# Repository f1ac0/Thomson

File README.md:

# Thomson
Kids in the 80's in France discovered computers at school with the TO and MO series from Thomson.

Interesting expansions exist to enjoy these systems, see below.

In this repository I share the boards I modified for my own needs, for example to use the parts I have in stock, or because I like my own routing.

# Disclaimer and Acknowledgements
This is a hobbyist project, it comes with no warranty and no support. Also remember that the Commodore machines are about 40 years old and may fail because of such hardware expansions.

I publish my work under the CC-BY-NC-SA license, unless stated otherwise. Thanks to everyone who share their knowledge and creations.

# Sources and interesting projects
## Cartridges
- https://dcmoto.pages-perso.free.fr/bricolage/memo7/index.html

## RAM
- https://www.forum.system-cfg.com/viewtopic.php?f=18&t=10807

## Expansions
- https://dcmoto.pages-perso.free.fr/bricolage/sddrive/index.html
- https://dcmoto.pages-perso.free.fr/bricolage/sx90-2018/index.html

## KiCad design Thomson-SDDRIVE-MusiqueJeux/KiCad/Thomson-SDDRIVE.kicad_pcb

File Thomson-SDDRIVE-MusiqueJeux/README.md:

# Thomson-SDDRIVE-MusiqueJeu
This is an expansion combining the SX90-018 "Contrôleur d'extensions modèle 2" that provides a 6 bit DAC for sound and two DB9 joystick ports and the SDDRIVE that emulates a floppy disk controller. The logic is integrated inside a XC9572XL CPLD and using SMD components to reduce size.

Warning : the two joystick ports use an "Atari" pinout and not the specific thomson-only pinout of the original expansion. Make sure to use standard controllers and not Thomson ones if you own any (I dont). 5V is present so you may use powered controllers, but make sure to use limited power to preserve your host PSU and motherboard.

# Disclaimer and Acknowledgements
This is a hobbyist project, it comes with no warranty and no support. Also remember that the Thomson machines are about 40 years old and may fail because of such hardware expansions.

The author of SDDRIVE keeps the intellectual property of his work and gracefully shares his degigns and agrees that users change, improve and share them, and forbids commercial use and selling the products. the content inside this folder is published under the same licensing terms.

It is not supported by the author of SDDRIVE, please don't bother him with issues you might have with it.

# From original designs by
- SDDRIVE by Daniel Coulom : https://dcmoto.pages-perso.free.fr/bricolage/sddrive/index.html
- SX90-018 by Thomson, schematics reverse engineered by Daniel Coulom for his SX90-2018 : https://dcmoto.pages-perso.free.fr/bricolage/sx90-2018/index.html
Thanks !

# Making it
Components are SMD, and have thin pin pitch. You need to know what you are doing.

Check for shorts at least between 5V, 3.3V, and GND traces before applying power ! I suggest to first install the CPLD and check its connections, then the PLCC socket and also check its connections, before the SD socket and through holes connectors that will maker rework more difficult.

Make sure to apply insulating tape under the SD socket where the contacts from the socket may touch the PCB. In order to keep the two layer PCB, this was not possible to use no copper zone there.

For the edge connector, I used a 2x21=42 pins connecto because I could not find an 2x19 one. If you do so then make sure to remove the four pins on the edges and insert a small piece of PCB to force the connector to be aligned with the PCB edge when inserted.

The ROM is oversized however easily available. You have to program it with the original sddrive_control.bin using an EEPROM programmer. Pad the end of the file up to a size of 524288 or tell your programmer to only burn the lower bytes since the higher addresses are grounded anyway.

Prepare the SDCARD as explained on the SDDRIVE page.

# Using it
Connect it to your Thomson. When the system is starting, it should show the disk drive menu that will start the selector. See the instructions for SDDRIVE, it should behave the same.

# FD2SD
You can use SD files that are compatible with your system. You will find some on the dcmoto website. You can also convert some .FD disk images.

The DCMOTO emulator provides a FD2SD windows tool, if you use a different system you may use the FD2SD in this repo.

Compile it with "gcc -o fd2sd fd2sd.c" then convert a file with "fd2sd file.fd". Check other usage with "fd2sd -h".

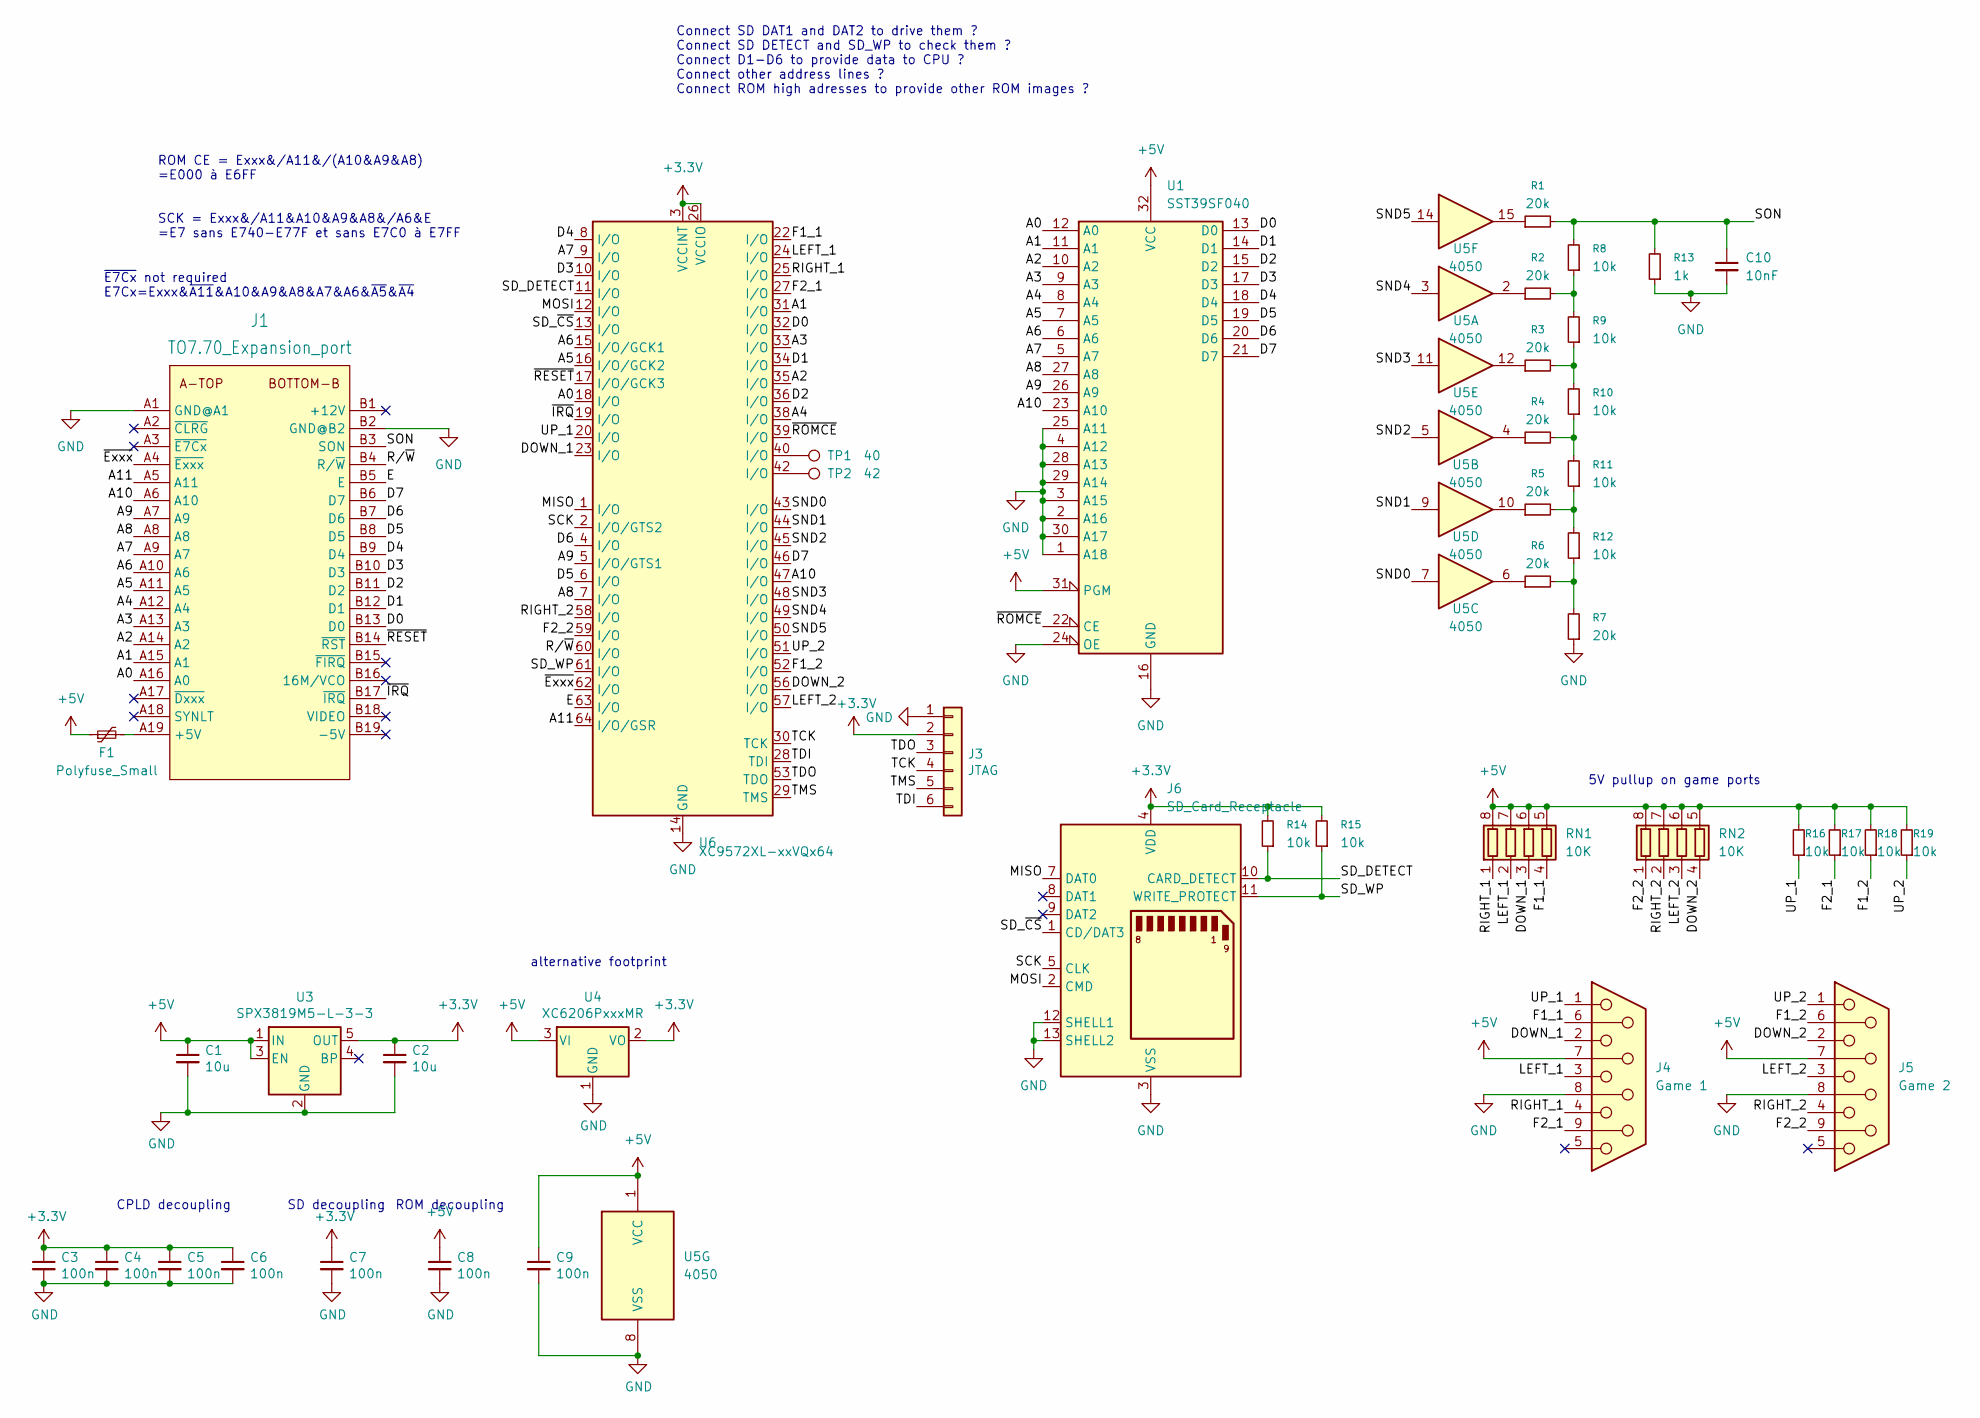
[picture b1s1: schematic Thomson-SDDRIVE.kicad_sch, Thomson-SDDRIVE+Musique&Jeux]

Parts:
C1, C2: 10u; C_0805_2012Metric
C3, C4, C5, C6, C7, C8, C9: 100n; C_0805_2012Metric
C10: 10nF; C_0805_2012Metric
F1: Polyfuse_Small; R_1210_3225Metric
J1: TO7.70_Expansion_port; TO7.70_Expansion_port_Minibus_3x19_P2.54mm_W5.08mm_Vertical
J3: JTAG; PinHeader_1x06_P2.54mm_Vertical
J4: Game 1; DSUB-9_Pins_Vertical_P2.77x2.84mm
J5: Game 2; DSUB-9_Pins_Vertical_P2.77x2.84mm
J6: SD_Card_Receptacle; Conn_SDcard_largerpads
R1, R2, R3, R4, R5, R6, R7: 20k; R_0805_2012Metric
R8, R9, R10, R11, R12, R14, R15, R16, R17, R18, R19: 10k; R_0805_2012Metric
R13: 1k; R_0805_2012Metric
RN1, RN2: 10K; R_Array_Convex_4x0603
TP1: 40; Measurement_Point_Round-SMD-Pad_VerySmall
TP2: 42; Measurement_Point_Round-SMD-Pad_VerySmall
U1: SST39SF040; PLCC-32_SMD-Socket
U3: SPX3819M5-L-3-3; SOT-23-5
U4: XC6206PxxxMR; SOT-23
U5: 4050; SOIC-16_3.9x9.9mm_P1.27mm
U6: XC9572XL-xxVQx64; TQFP-64_10x10mm_P0.5mm

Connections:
+3.3V: C2.1, C3.1, C4.1, C5.1, C6.1, C7.1, J3.2, J6.4 (VDD), R14.2, R15.2, U3.5 (OUT), U4.2 (VO), U6.3 (VCCINT), U6.26 (VCCIO), U6.37 (VCCINT), U6.55 (VCCIO)
+5V: C1.1, C8.1, C9.1, F1.1, J4.7, J5.7, R16.2, R17.2, R18.2, R19.2, RN1.5 (R4.2), RN1.6 (R3.2), RN1.7 (R2.2), RN1.8 (R1.2), RN2.5 (R4.2), RN2.6 (R3.2), RN2.7 (R2.2), RN2.8 (R1.2), U1.31 (PGM), U1.32 (VCC), U3.1 (IN), U3.3 (EN), U4.3 (VI), U5.1 (VCC)
/A0: J1.A16 (A0), U1.12 (A0), U6.18 (I/O)
/A1: J1.A15 (A1), U1.11 (A1), U6.31 (I/O)
/A2: J1.A14 (A2), U1.10 (A2), U6.35 (I/O)
/A3: J1.A13 (A3), U1.9 (A3), U6.33 (I/O)
/A4: J1.A12 (A4), U1.8 (A4), U6.38 (I/O)
/A5: J1.A11 (A5), U1.7 (A5), U6.16 (I/O/GCK2)
/A6: J1.A10 (A6), U1.6 (A6), U6.15 (I/O/GCK1)
/A7: J1.A9 (A7), U1.5 (A7), U6.9 (I/O)
/A8: J1.A8, U1.27 (A8), U6.7 (I/O)
/A9: J1.A7 (A9), U1.26 (A9), U6.5 (I/O/GTS1)
/A10: J1.A6 (A10), U1.23 (A10), U6.47 (I/O)
/A11: J1.A5 (A11), U6.64 (I/O/GSR)
/D0: J1.B13 (D0), U1.13 (D0), U6.32 (I/O)
/D1: J1.B12 (D1), U1.14 (D1), U6.34 (I/O)
/D2: J1.B11 (D2), U1.15 (D2), U6.36 (I/O)
/D3: J1.B10 (D3), U1.17 (D3), U6.10 (I/O)
/D4: J1.B9 (D4), U1.18 (D4), U6.8 (I/O)
/D5: J1.B8 (D5), U1.19 (D5), U6.6 (I/O)
/D6: J1.B7 (D6), U1.20 (D6), U6.4 (I/O)
/D7: J1.B6 (D7), U1.21 (D7), U6.46 (I/O)
/DOWN_1: J4.2, RN1.3 (R3.1), U6.23 (I/O)
/DOWN_2: J5.2, RN2.4 (R4.1), U6.56 (I/O)
/E: J1.B5 (E), U6.63 (I/O)
/F1_1: J4.6, RN1.4 (R4.1), U6.22 (I/O)
/F1_2: J5.6, R18.1, U6.52 (I/O)
/F2_1: J4.9, R17.1, U6.27 (I/O)
/F2_2: J5.9, RN2.1 (R1.1), U6.59 (I/O)
/LEFT_1: J4.3, RN1.2 (R2.1), U6.24 (I/O)
/LEFT_2: J5.3, RN2.3 (R3.1), U6.57 (I/O)
/MISO: J6.7 (DAT0), U6.1 (I/O)
/MOSI: J6.2 (CMD), U6.12 (I/O)
/RIGHT_1: J4.4, RN1.1 (R1.1), U6.25 (I/O)
/RIGHT_2: J5.4, RN2.2 (R2.1), U6.58 (I/O)
/R/~W: J1.B4 (R/~W), U6.60 (I/O)
/SCK: J6.5 (CLK), U6.2 (I/O/GTS2)
/SD_DETECT: J6.10 (CARD_DETECT), R14.1, U6.11 (I/O)
/SD_WP: J6.11 (WRITE_PROTECT), R15.1, U6.61 (I/O)
/SD_~CS: J6.1 (CD/DAT3), U6.13 (I/O)
/SND0: U5.7, U6.43 (I/O)
/SND1: U5.9, U6.44 (I/O)
/SND2: U5.5, U6.45 (I/O)
/SND3: U5.11, U6.48 (I/O)
/SND4: U5.3, U6.49 (I/O)
/SND5: U5.14, U6.50 (I/O)
/SON: C10.1, J1.B3 (SON), R1.2, R8.2, R13.2
/TCK: J3.4, U6.30 (TCK)
/TDI: J3.6, U6.28 (TDI)
/TDO: J3.3, U6.53 (TDO)
/TMS: J3.5, U6.29 (TMS)
/UP_1: J4.1, R16.1, U6.20 (I/O)
/UP_2: J5.1, R19.1, U6.51 (I/O)
/~Exxx: J1.A4 (~Exxx), U6.62 (I/O)
/~IRQ: J1.B17 (~IRQ), U6.19 (I/O)
/~RESET: J1.B14 (~RST), U6.17 (I/O/GCK3)
/~ROMCE: U1.22 (CE), U6.39 (I/O)
GND: C1.2, C2.2, C3.2, C4.2, C5.2, C6.2, C7.2, C8.2, C9.2, C10.2, J1.A1 (GND@A1), J1.B2 (GND@B2), J3.1, J4.8, J5.8, J6.3 (VSS), J6.6 (VSS), J6.12 (SHELL1), J6.13 (SHELL2), R7.1, R13.1, U1.1 (A18), U1.2 (A16), U1.3 (A15), U1.4 (A12), U1.16 (GND), U1.24 (OE), U1.25 (A11), U1.28 (A13), U1.29 (A14), U1.30 (A17), U3.2 (GND), U4.1 (GND), U5.8 (VSS), U6.14 (GND), U6.21 (GND), U6.41 (GND), U6.54 (GND)
unnamed: F1.2, J1.A19 (+5V)
unnamed: R1.1, U5.15
unnamed: R2.1, U5.2
unnamed: R2.2, R8.1, R9.2
unnamed: R3.1, U5.12
unnamed: R4.1, U5.4
unnamed: R5.1, U5.10
unnamed: R6.1, U5.6
unnamed: R4.2, R10.1, R11.2
unnamed: R3.2, R9.1, R10.2
unnamed: R5.2, R11.1, R12.2
unnamed: R6.2, R7.2, R12.1
unnamed: TP1.1, U6.40 (I/O)
unnamed: TP2.1, U6.42 (I/O)

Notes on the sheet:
~{E7Cx} not required E7Cx=Exxx&~{A11}&A10&A9&A8&A7&A6&~{A5}&~{A4}
5V pullup on game ports
SD decoupling
ROM CE = Exxx&/A11&/(A10&A9&A8) =E000 à E6FF SCK = Exxx&/A11&A10&A9&A8&/A6&E =E7 sans E740-E77F et sans E7C0 à E7FF
alternative footprint
CPLD decoupling
Connect SD DAT1 and DAT2 to drive them ? Connect SD DETECT and SD_WP to check them ? Connect D1-D6 to provide data to CPU ? Connect other address lines ? Connect ROM high adresses to provide other ROM images ?
ROM decoupling

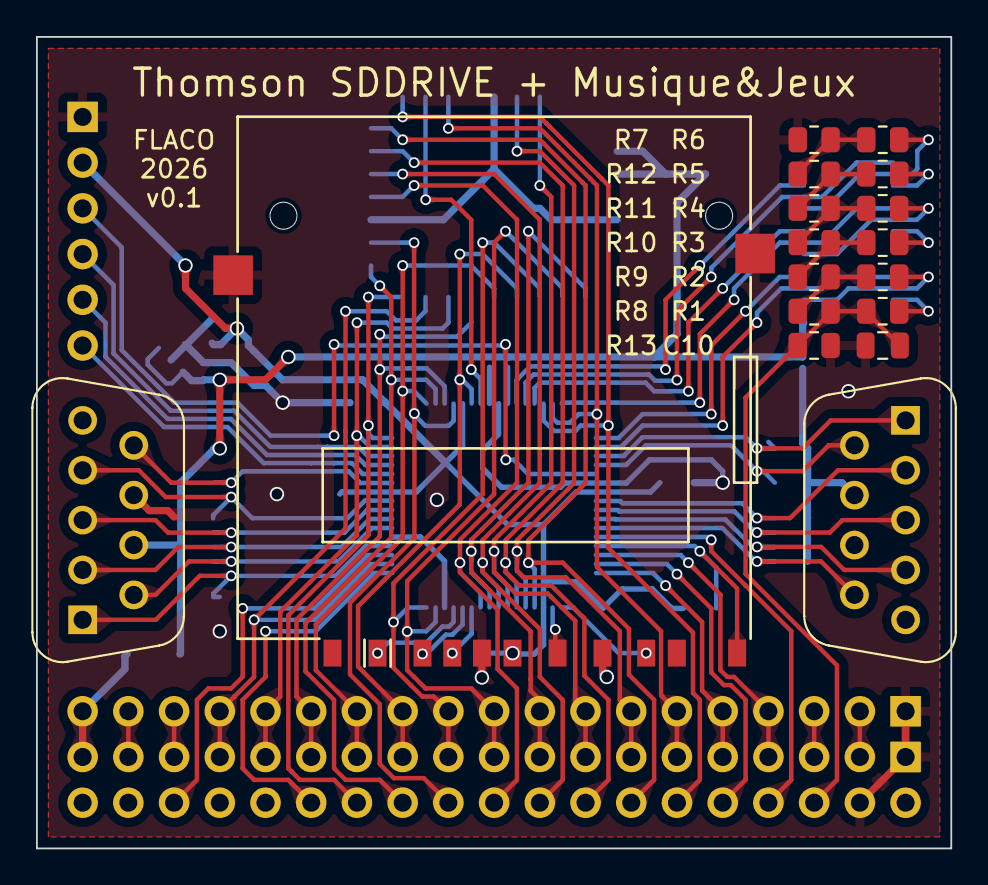
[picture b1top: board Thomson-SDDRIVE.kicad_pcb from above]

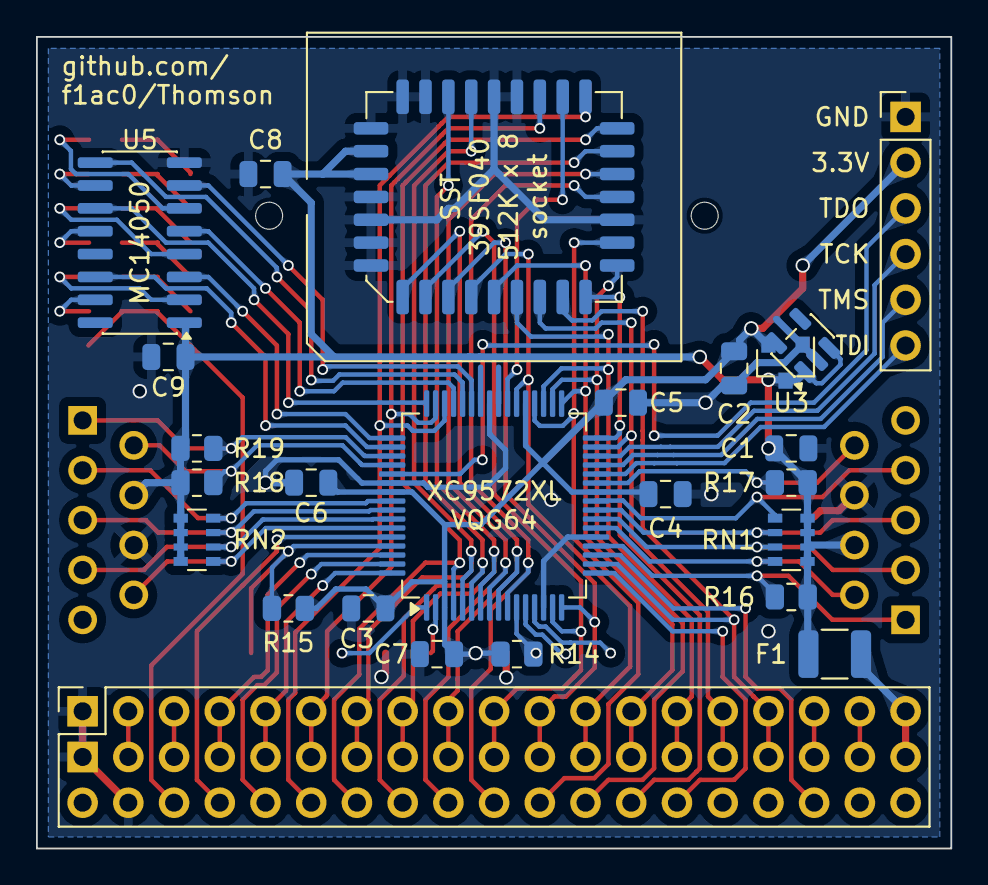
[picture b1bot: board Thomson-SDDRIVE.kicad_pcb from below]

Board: 2 copper layers, 50.8 x 45.1 mm, 42 parts (25 on the bottom side), 70 nets.

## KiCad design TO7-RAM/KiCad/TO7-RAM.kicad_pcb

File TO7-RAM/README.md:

# TO7-RAM
A 64K RAM for the TO7/70, adding 4 banks of 16kB. Basic 128 now reports 128K of RAM and TEST64K-TO770 Memo7 says banks 2-7 are OK. Not sure it is useful for anything else yet.

# Disclaimer and Acknowledgements
This is a hobbyist project, it comes with no warranty and no support. Also remember that the Commodore machines are about 40 years old and may fail because of such hardware expansions.

I publish my work under the CC-BY-NC-SA license, unless stated otherwise. Thanks to everyone who share their knowledge and creations.

# Original design
- https://www.forum.system-cfg.com/viewtopic.php?f=18&t=10807
Thanks 6502man, Daniel and Fred_72 !

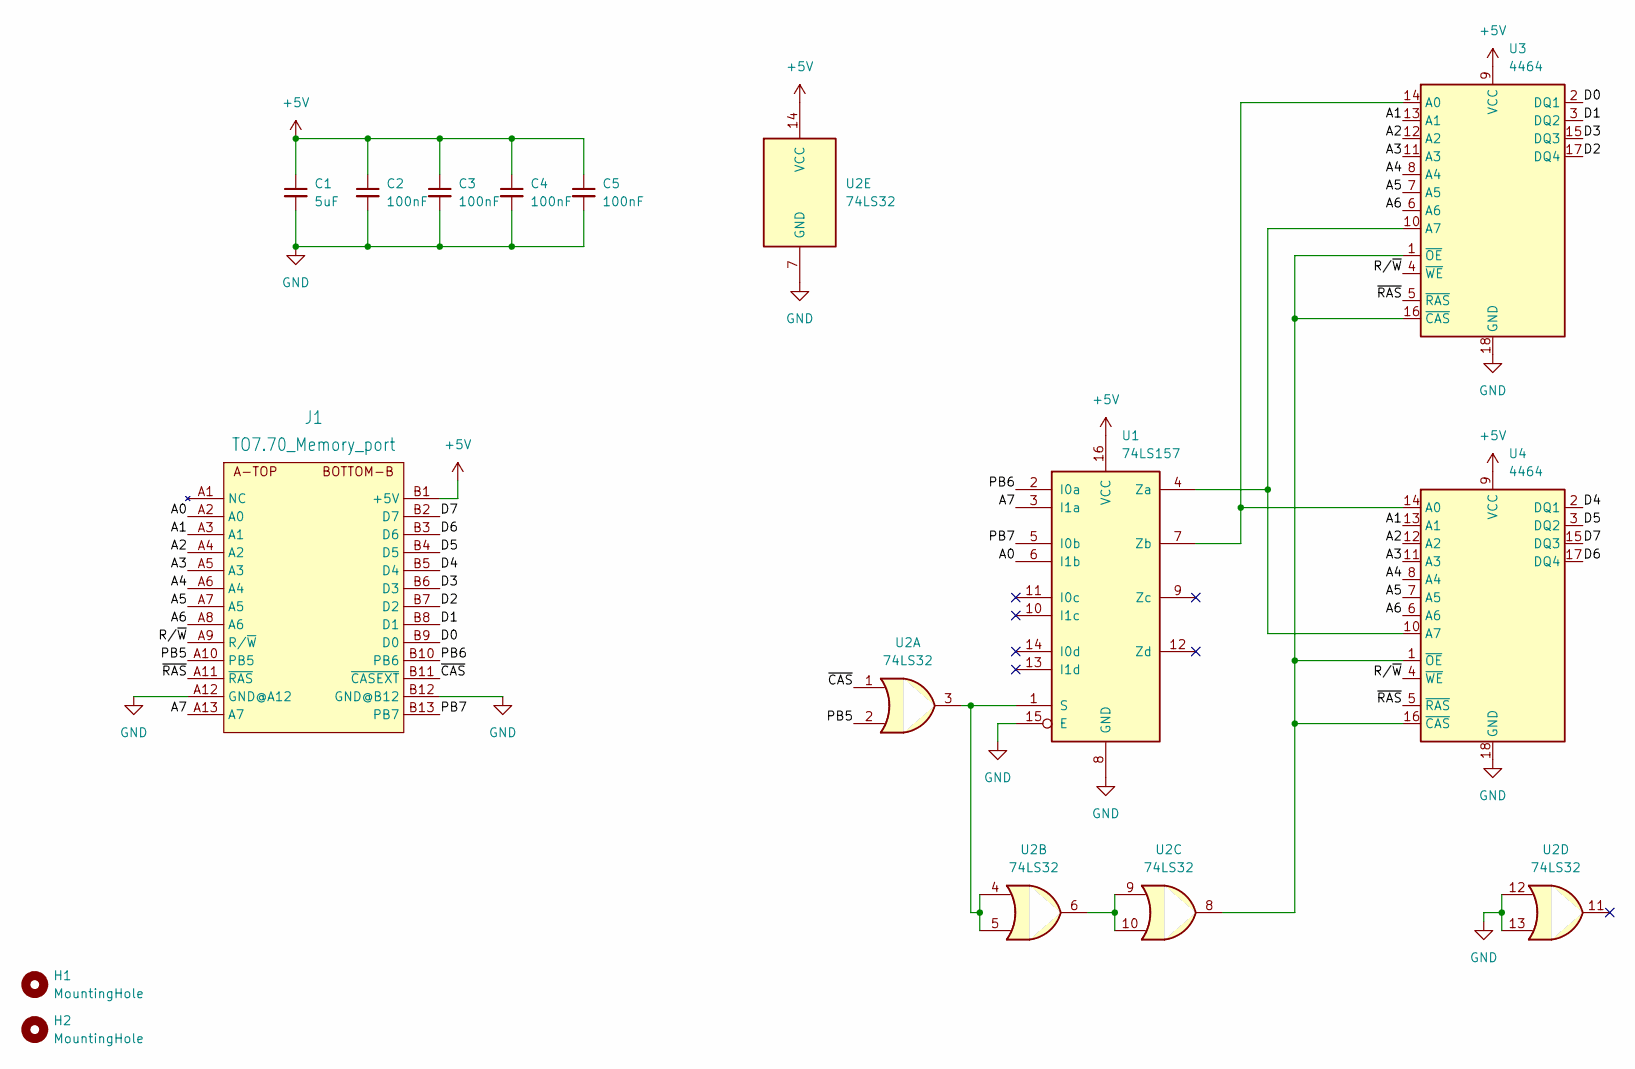
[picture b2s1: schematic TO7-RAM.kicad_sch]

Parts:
C1: 5uF; C_0805_2012Metric
C2, C3, C4, C5: 100nF; C_0805_2012Metric
H1, H2: MountingHole; MountingHole_4mm
J1: TO7.70_Memory_port; TO7.70_Memory_port_2x13_P2.54mm_W5.08mm_Vertical
U1: 74LS157; DIP-16_W7.62mm
U2: 74LS32; DIP-14_W7.62mm
U3, U4: 4464; DIP-18_W7.62mm_Socket

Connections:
+5V: C1.1, C2.1, C3.1, C4.1, C5.1, J1.B1 (+5V), U1.16 (VCC), U2.14 (VCC), U3.9 (VCC), U4.9 (VCC)
/A0: J1.A2 (A0), U1.6 (I1b)
/A1: J1.A3 (A1), U3.13 (A1), U4.13 (A1)
/A2: J1.A4 (A2), U3.12 (A2), U4.12 (A2)
/A3: J1.A5 (A3), U3.11 (A3), U4.11 (A3)
/A4: J1.A6 (A4), U3.8 (A4), U4.8 (A4)
/A5: J1.A7 (A5), U3.7 (A5), U4.7 (A5)
/A6: J1.A8 (A6), U3.6 (A6), U4.6 (A6)
/A7: J1.A13 (A7), U1.3 (I1a)
/D0: J1.B9 (D0), U3.2 (DQ1)
/D1: J1.B8 (D1), U3.3 (DQ2)
/D2: J1.B7 (D2), U3.17 (DQ4)
/D3: J1.B6 (D3), U3.15 (DQ3)
/D4: J1.B5 (D4), U4.2 (DQ1)
/D5: J1.B4 (D5), U4.3 (DQ2)
/D6: J1.B3 (D6), U4.17 (DQ4)
/D7: J1.B2 (D7), U4.15 (DQ3)
/PB5: J1.A10 (PB5), U2.2
/PB6: J1.B10 (PB6), U1.2 (I0a)
/PB7: J1.B13 (PB7), U1.5 (I0b)
/R/~W: J1.A9 (R/~W), U3.4 (~WE), U4.4 (~WE)
/~CAS: J1.B11 (~CASEXT), U2.1
/~RAS: J1.A11 (~RAS), U3.5 (~RAS), U4.5 (~RAS)
GND: C1.2, C2.2, C3.2, C4.2, C5.2, J1.A12 (GND@A12), J1.B12 (GND@B12), U1.8 (GND), U1.15 (E), U2.7 (GND), U2.12, U2.13, U3.18 (GND), U4.18 (GND)
unnamed: U1.1 (S), U2.3, U2.4, U2.5
unnamed: U1.4 (Za), U3.10 (A7), U4.10 (A7)
unnamed: U1.7 (Zb), U3.14 (A0), U4.14 (A0)
unnamed: U2.6, U2.9, U2.10
unnamed: U2.8, U3.1 (~OE), U3.16 (~CAS), U4.1 (~OE), U4.16 (~CAS)

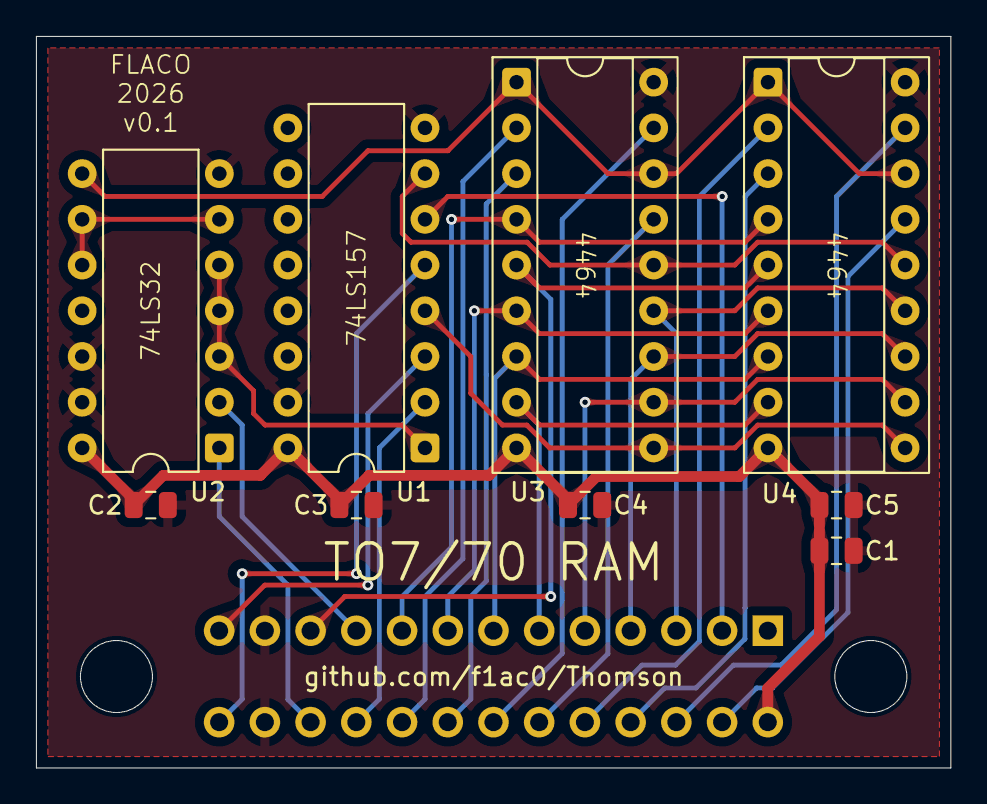
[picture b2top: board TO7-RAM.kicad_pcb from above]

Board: 2 copper layers, 50.8 x 40.6 mm, 12 parts (1 on the bottom side), 29 nets.

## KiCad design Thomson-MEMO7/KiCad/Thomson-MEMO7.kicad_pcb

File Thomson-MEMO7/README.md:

# Thomson-MEMO7
A multi-ROM Memo7 for the TO7 computer.
- 32x 16k banks
- 32k and 64k using bank switching
- 3D printed case

# Disclaimer and Acknowledgements
This is a hobbyist project, it comes with no warranty and no support. Also remember that the Commodore machines are about 40 years old and may fail because of such hardware expansions.

I publish my work under the CC-BY-NC-SA license, unless stated otherwise. Thanks to everyone who share their knowledge and creations.

# Inspired by
- https://dcmoto.pages-perso.free.fr/bricolage/memo7/index.html
- https://forum.system-cfg.com/viewtopic.php?f=10&t=7086
- https://www.thingiverse.com/thing:5231941
Thanks !

# Making it
- Install the DIP switch so that the switches are closed when the lever is LOW
- Check for shorts at least between 5V, and GND traces before applying power! Also check that R4 and R5 are not shorted : if they are then the pins of the ROM socket are shorted to the nearby 5V pin and setting A17/A18 switch to LOW will short 5V to ground!

To prepare the ROM image,
- select 16k, 32k and 64k files to fill the 512k ROM chip and decide their order in the ROM,
- for 32k and 64k files, make sure they will start respectively on 32k and 64k boundaries,
- for 4k and 8k file, duplicate them 4 times and 2 times respectively,
- for files that are shorter than 16k, pad them up to the full size,
- concatenate them into one single file,
- burn the file into the EEPROM.

For example on linux : cat 16krom.m7 4krom.m7 4krom.m7 4krom.m7 4krom.m7 32krom.m7 64krom.m7 (...) >romfile

I suggest to print the content of the ROM with the correct switch placement to remember it later:
- LLLLLHH 16krom
- LLLLHHH 4krom
- LLLHHLH 32krom
- LLHHHLL 64krom
- ...

# Using it
Choose the ROM while the system is powered down.
- To select a 16k ROM, dial its address on the A14 to A18 switches. Set the 32k and 64k switches UP.
- To select a 32K ROM, dial its address on the A15 to A18 switches. Set A14 UP and 32k LOW.
- To select a 64K ROM, dial its address on the A16 to A18 switches. Set A14 and A15 UP then 32k and 64k LOW.

Make sure to always set A14 UP when 32K is LOW, and A15 UP when 64k is LOW: failing to do so and setting them LOW at the same time will short to ground the outputs of the 74LS173 and may damage them.

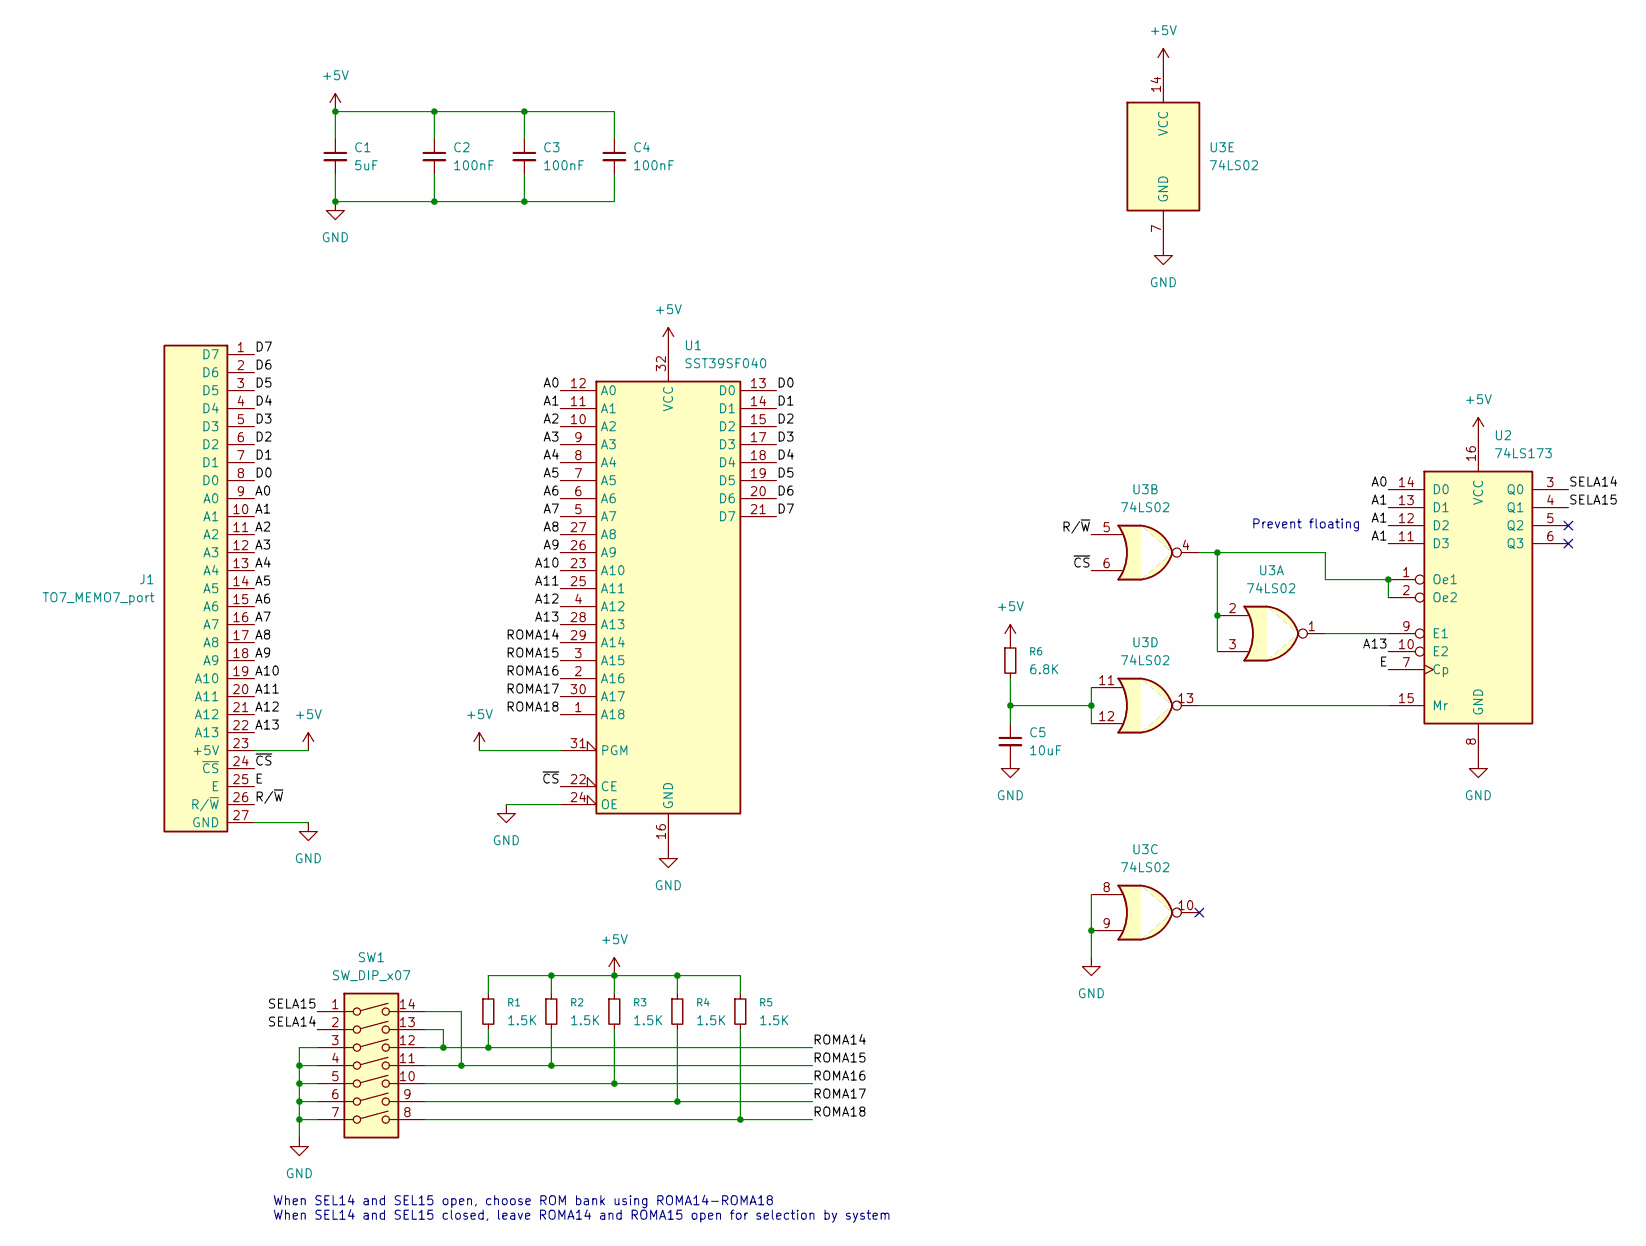
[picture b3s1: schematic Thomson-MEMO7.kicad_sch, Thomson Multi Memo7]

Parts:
C1: 5uF; C_0805_2012Metric
C2, C3, C4: 100nF; C_0805_2012Metric
C5: 10uF; C_0805_2012Metric
J1: TO7_MEMO7_port; TO7_MEMO7
R1, R2, R3, R4, R5: 1.5K; R_0805_2012Metric
R6: 6.8K; R_0805_2012Metric
SW1: SW_DIP_x07; SW_DIP_SPSTx07_Slide_9.78x19.96mm_W7.62mm_P2.54mm
U1: SST39SF040; PLCC-32_SMD-Socket
U2: 74LS173; DIP-16_W7.62mm
U3: 74LS02; DIP-14_W7.62mm

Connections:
+5V: C1.1, C2.1, C3.1, C4.1, J1.23 (+5V), R1.1, R2.1, R3.1, R4.1, R5.1, R6.1, U1.31 (PGM), U1.32 (VCC), U2.16 (VCC), U3.14 (VCC)
/A0: J1.9 (A0), U1.12 (A0), U2.14 (D0)
/A1: J1.10 (A1), U1.11 (A1), U2.11 (D3), U2.12 (D2), U2.13 (D1)
/A2: J1.11 (A2), U1.10 (A2)
/A3: J1.12 (A3), U1.9 (A3)
/A4: J1.13 (A4), U1.8 (A4)
/A5: J1.14 (A5), U1.7 (A5)
/A6: J1.15 (A6), U1.6 (A6)
/A7: J1.16 (A7), U1.5 (A7)
/A8: J1.17 (A8), U1.27 (A8)
/A9: J1.18 (A9), U1.26 (A9)
/A10: J1.19 (A10), U1.23 (A10)
/A11: J1.20 (A11), U1.25 (A11)
/A12: J1.21 (A12), U1.4 (A12)
/A13: J1.22 (A13), U1.28 (A13), U2.10 (E2)
/D0: J1.8 (D0), U1.13 (D0)
/D1: J1.7 (D1), U1.14 (D1)
/D2: J1.6 (D2), U1.15 (D2)
/D3: J1.5 (D3), U1.17 (D3)
/D4: J1.4 (D4), U1.18 (D4)
/D5: J1.3 (D5), U1.19 (D5)
/D6: J1.2 (D6), U1.20 (D6)
/D7: J1.1 (D7), U1.21 (D7)
/E: J1.25 (E), U2.7 (Cp)
/ROMA14: R1.2, SW1.12, SW1.13, U1.29 (A14)
/ROMA15: R2.2, SW1.11, SW1.14, U1.3 (A15)
/ROMA16: R3.2, SW1.10, U1.2 (A16)
/ROMA17: R4.2, SW1.9, U1.30 (A17)
/ROMA18: R5.2, SW1.8, U1.1 (A18)
/R/~W: J1.26 (R/~W), U3.5
/SELA14: SW1.2, U2.3 (Q0)
/SELA15: SW1.1, U2.4 (Q1)
/~CS: J1.24 (~CS), U1.22 (CE), U3.6
GND: C1.2, C2.2, C3.2, C4.2, C5.2, J1.27 (GND), SW1.3, SW1.4, SW1.5, SW1.6, SW1.7, U1.16 (GND), U1.24 (OE), U2.8 (GND), U3.7 (GND), U3.8, U3.9
unnamed: C5.1, R6.2, U3.11, U3.12
unnamed: U2.9 (E1), U3.1
unnamed: U2.15 (Mr), U3.13
unnamed: U2.1 (Oe1), U2.2 (Oe2), U3.2, U3.3, U3.4

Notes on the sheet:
Prevent floating
When SEL14 and SEL15 open, choose ROM bank using ROMA14-ROMA18 When SEL14 and SEL15 closed, leave ROMA14 and ROMA15 open for selection by system

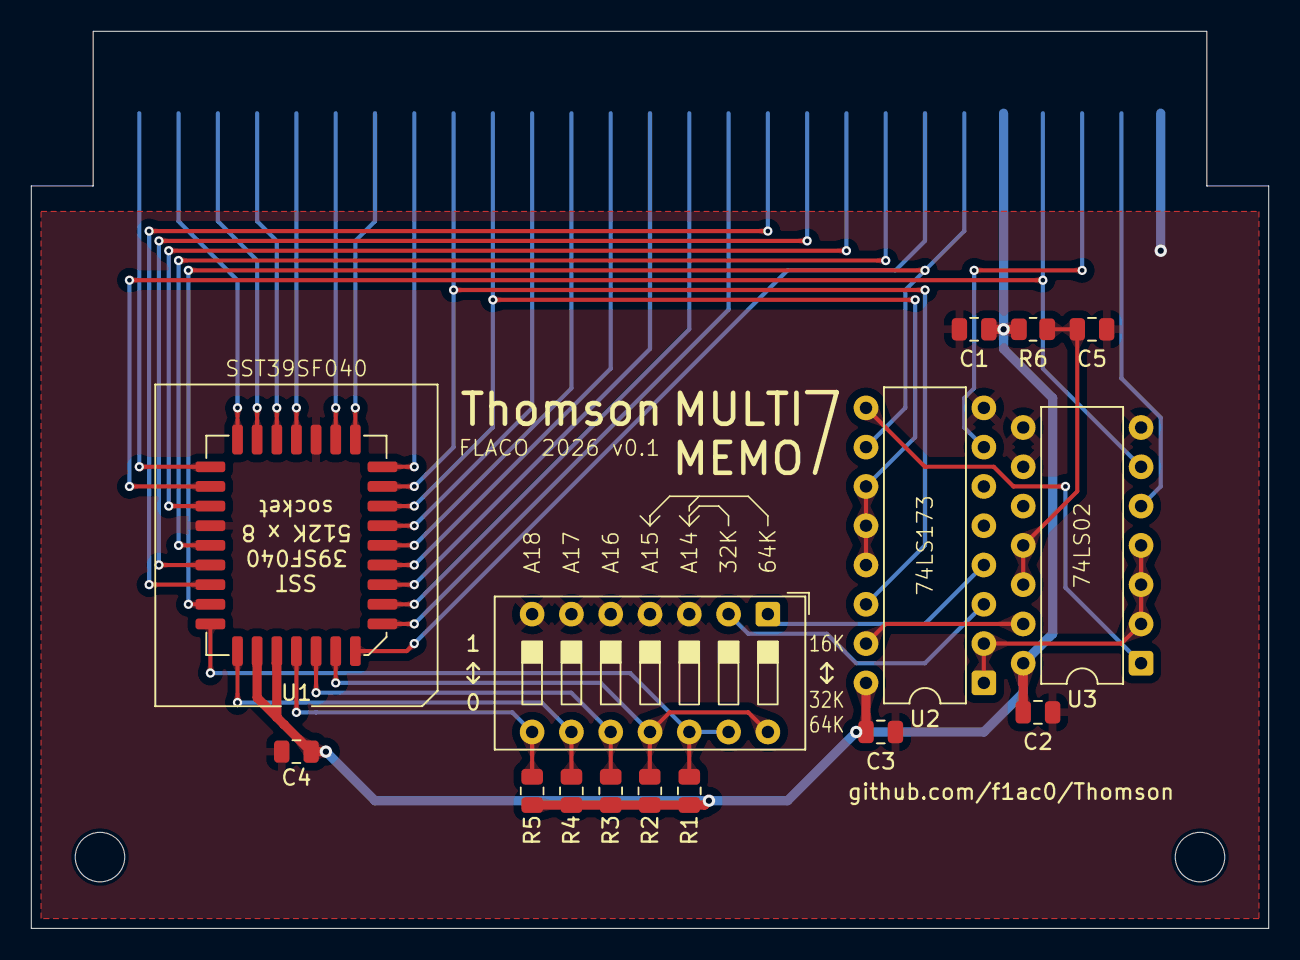
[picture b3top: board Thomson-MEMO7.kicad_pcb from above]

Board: 2 copper layers, 80.0 x 58.0 mm, 16 parts (1 on the bottom side), 38 nets.

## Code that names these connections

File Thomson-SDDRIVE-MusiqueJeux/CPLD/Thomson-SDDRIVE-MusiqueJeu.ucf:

PIN "E"	LOC = P63;
PIN "RW"	LOC = P60;
PIN "D<0>"	LOC = P32;
PIN "D<1>"	LOC = P34;
PIN "D<2>"	LOC = P36;
PIN "D<3>"	LOC = P10;
PIN "D<4>"	LOC = P8;
PIN "D<5>"	LOC = P6;
PIN "D<6>"	LOC = P4;
PIN "D<7>"	LOC = P46;
PIN "_CSE"	LOC = P62;
PIN "A<0>"	LOC = P18;
PIN "A<1>"	LOC = P31;
PIN "A<2>"	LOC = P35;
PIN "A<3>"	LOC = P33;
PIN "A<4>"	LOC = P38;
PIN "A<5>"	LOC = P16;
PIN "A<6>"	LOC = P15;
PIN "A<7>"	LOC = P9;
PIN "A<8>"	LOC = P7;
PIN "A<9>"	LOC = P5;
PIN "A<10>"	LOC = P47;
PIN "A<11>"	LOC = P64;
PIN "_IRQ"	LOC = P19;
PIN "_RST"	LOC = P17;
PIN "_ROMCE"	LOC = P39;
PIN "SD_CS"	LOC = P13;
PIN "SD_SCK"	LOC = P2;
PIN "SD_MOSI"	LOC = P12;
PIN "SD_MISO"	LOC = P1;
PIN "SON<0>"	LOC = P43;
PIN "SON<1>"	LOC = P44;
PIN "SON<2>"	LOC = P45;
PIN "SON<3>"	LOC = P48;
PIN "SON<4>"	LOC = P49;
PIN "SON<5>"	LOC = P50;
PIN "J1<0>"	LOC = P20;
PIN "J1<1>"	LOC = P23;
PIN "J1<2>"	LOC = P24;
PIN "J1<3>"	LOC = P25;
PIN "J1<4>"	LOC = P22;
PIN "J1<5>"	LOC = P27;
PIN "J2<0>"	LOC = P51;
PIN "J2<1>"	LOC = P56;
PIN "J2<2>"	LOC = P57;
PIN "J2<3>"	LOC = P58;
PIN "J2<4>"	LOC = P52;
PIN "J2<5>"	LOC = P59;

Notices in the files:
TO7-RAM/KiCad/TO7-RAM.kicad_pcb:
FLACO 2026, CC-BY-NC-SA
